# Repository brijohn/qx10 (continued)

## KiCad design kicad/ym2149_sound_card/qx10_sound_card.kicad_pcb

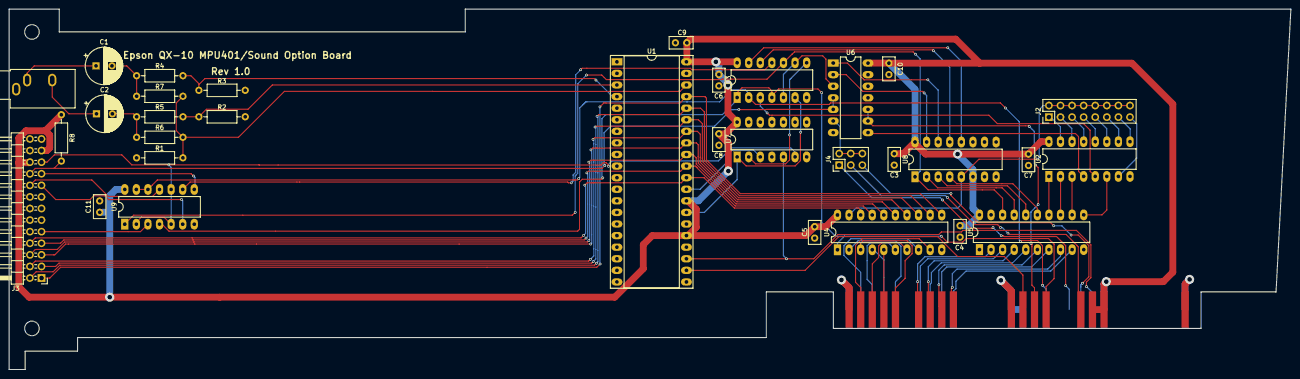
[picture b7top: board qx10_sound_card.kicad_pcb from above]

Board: 2 copper layers, 281.0 x 79.0 mm, 33 parts (0 on the bottom side), 76 nets.

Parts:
C1, C2: 470uF; CP_Radial_D8.0mm_P3.50mm
C3, C4, C5, C6, C7, C8, C9, C10, C11: .1uF; C_Disc_D5.0mm_W2.5mm_P2.50mm
CN1: Edge Connector; BUS_QX10
J1: Speakers; Jack_3.5mm_CUI_SJ1-3533NG_Horizontal
J2: Base Address; PinHeader_2x08_P2.54mm_Vertical
J3: MPU401; PinHeader_2x13_P2.54mm_Horizontal
J4: INT Select; PinHeader_2x03_P2.54mm_Vertical
R1, R2, R3: 3K; R_Axial_DIN0207_L6.3mm_D2.5mm_P10.16mm_Horizontal
R4, R5: 1K; R_Axial_DIN0207_L6.3mm_D2.5mm_P10.16mm_Horizontal
R6, R7: 1K6; R_Axial_DIN0207_L6.3mm_D2.5mm_P10.16mm_Horizontal
R8: 1k; R_Axial_DIN0207_L6.3mm_D2.5mm_P10.16mm_Horizontal
U1: YM2149; DIP-40_W15.24mm_Socket_LongPads
U2, U8: 74LS138; DIP-16_W7.62mm_LongPads
U3, U9: 74LS08; DIP-14_W7.62mm_LongPads
U4: 74LS245; DIP-20_W7.62mm_LongPads
U5: 74LS541; DIP-20_W7.62mm_LongPads
U6: 74LS00; DIP-14_W7.62mm_LongPads
U7: 74LS86; DIP-14_W7.62mm_LongPads

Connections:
+5V: C3.1, C4.1, C5.1, C6.1, C7.1, C8.1, C9.1, C10.1, C11.1, CN1.43, CN1.45, CN1.46, J3.22, J3.23, R8.1, U1.25, U1.28, U1.40, U2.16, U3.14, U4.20, U5.20, U6.14, U7.14, U8.6, U8.16, U9.14
/A0: U3.10, U5.18, U8.1, U9.1
/A1: U5.17, U8.2
/A2: U5.16, U8.3
/A3: U5.15, U8.4
/A4: U2.1, U5.14
/A5: U2.2, U5.13
/A6: U2.3, U5.12
/A7: U2.6, U5.11
/ADR0: CN1.13, U5.2
/ADR1: CN1.14, U5.3
/ADR2: CN1.15, U5.4
/ADR3: CN1.16, U5.5
/ADR4: CN1.17, U5.6
/ADR5: CN1.18, U5.7
/ADR6: CN1.19, U5.8
/ADR7: CN1.20, U5.9
/BC1: U1.29, U7.3
/BDIR: U1.27, U3.6, U7.1
/CHANA: R2.1, R5.2, U1.3
/CHANB: R3.1, R4.2, U1.4
/CHANC: R1.1, R6.2, R7.2, U1.38
/CLK: CN1.31, U1.22
/D0: J3.1, U1.37, U4.11
/D1: J3.2, U1.36, U4.12
/D2: J3.3, U1.35, U4.13
/D3: J3.4, U1.34, U4.14
/D4: J3.5, U1.33, U4.15
/D5: J3.6, U1.32, U4.16
/D6: J3.7, U1.31, U4.17
/D7: J3.8, U1.30, U4.18
/DTB0: CN1.3, U4.9
/DTB1: CN1.4, U4.8
/DTB2: CN1.5, U4.7
/DTB3: CN1.6, U4.6
/DTB4: CN1.7, U4.5
/DTB5: CN1.8, U4.4
/DTB6: CN1.9, U4.3
/DTB7: CN1.10, U4.2
/INTH1: CN1.40, J4.1
/INTH2: CN1.41, J4.3
/INTL: CN1.42, J4.5
/~BSAK: CN1.33, U6.9, U6.10
/~CS: J2.2, J2.4, J2.6, J2.8, J2.10, J2.12, J2.14, J2.16, U4.19, U8.5
/~IRD: CN1.35, U3.1, U3.4, U4.1, U9.4
/~IRQ: J3.20, R8.2, U6.4, U6.5
/~IWR: CN1.36, U3.2, U9.12, U9.13
/~MPU401: U3.11, U9.9
/~RESET: CN1.44, U1.23, U7.5
/~RSET: J3.21, U7.6, U9.2, U9.5, U9.10
/~WR: J3.18, U9.11
GND: C3.2, C4.2, C5.2, C6.2, C7.2, C8.2, C9.2, C10.2, C11.2, CN1.1, CN1.2, CN1.29, CN1.30, CN1.32, CN1.59, CN1.60, J1.S, J3.10, J3.11, J3.24, J3.25, R1.2, R2.2, R3.2, U1.1, U1.24, U1.26, U2.8, U3.7, U4.10, U5.1, U5.10, U5.19, U6.7, U6.12, U6.13, U7.4, U7.7, U7.9, U7.10, U7.12, U7.13, U8.8, U9.7
unnamed: C1.1, J1.T
unnamed: C1.2, R4.1, R7.1
unnamed: C2.1, J1.R
unnamed: C2.2, R5.1, R6.1
unnamed: J2.1, U2.15
unnamed: J2.3, U2.14
unnamed: J2.5, U2.13
unnamed: J2.7, U2.12
unnamed: J2.9, U2.11
unnamed: J2.11, U2.10
unnamed: J2.13, U2.9
unnamed: J2.15, U2.7
unnamed: J3.9, U9.3
unnamed: J3.17, U9.6
unnamed: J3.19, U9.8
unnamed: J4.2, J4.4, J4.6, U6.6
unnamed: U2.4, U6.8
unnamed: U2.5, U3.3
unnamed: U3.5, U3.9, U6.3
unnamed: U3.8, U7.2
unnamed: U3.12, U8.13
unnamed: U3.13, U8.12
unnamed: U6.1, U8.14
unnamed: U6.2, U8.15

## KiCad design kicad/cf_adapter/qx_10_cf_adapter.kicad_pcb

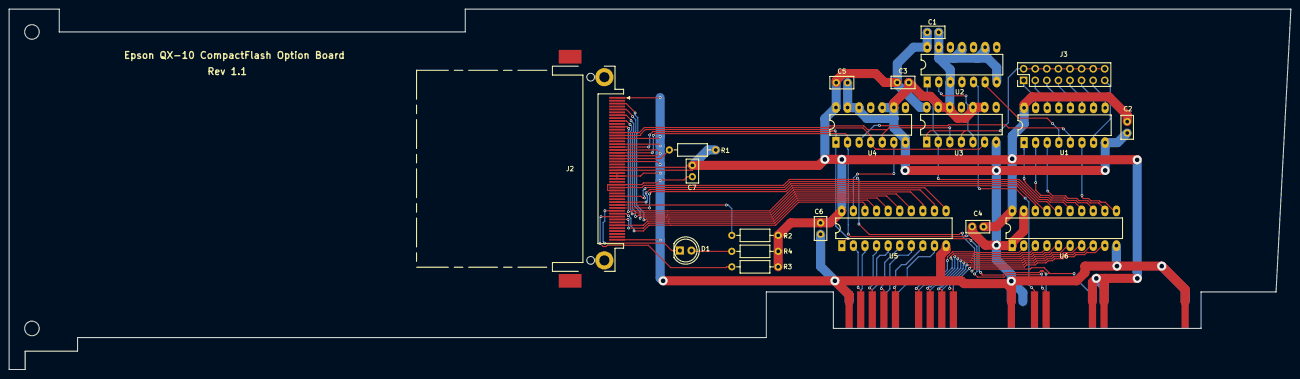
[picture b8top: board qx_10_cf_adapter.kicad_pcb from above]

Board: 2 copper layers, 281.0 x 79.0 mm, 21 parts (0 on the bottom side), 58 nets.

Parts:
C1, C2, C3, C4, C5, C6, C7: .1uf; C_Disc_D5.0mm_W2.5mm_P2.50mm
D1: LED; LED_D5.0mm
J1: Edge Connector; BUS_QX10
J2: CF Connector; CF-Card_3M_N7E50-7516PK-20-WF
J3: Address Jumper; PinHeader_2x08_P2.54mm_Vertical
R1, R2, R3, R4: 1k; R_Axial_DIN0207_L6.3mm_D2.5mm_P10.16mm_Horizontal
U1: 74LS138; DIP-16_W7.62mm_LongPads
U2: 74LS04; DIP-14_W7.62mm_LongPads
U3: 74LS32; DIP-14_W7.62mm_LongPads
U4: 74LS08; DIP-14_W7.62mm_LongPads
U5: 74LS245; DIP-20_W7.62mm_LongPads
U6: 74LS541; DIP-20_W7.62mm_LongPads

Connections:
+5V: C1.1, C2.1, C3.1, C4.1, C5.1, C6.1, C7.1, J1.43, J1.45, J1.46, J2.13, J2.38, R1.1, R2.1, R3.1, R4.1, U1.16, U2.14, U3.14, U4.14, U5.20, U6.20
/A0: J2.20, U6.18
/A1: J2.19, U6.17
/A2: J2.18, U6.16
/A3: U2.1, U3.2, U6.15
/A4: U1.1, U6.14
/A5: U1.2, U6.13
/A6: U1.3, U6.12
/A7: U1.6, U6.11
/ADR0: J1.13, U6.2
/ADR1: J1.14, U6.3
/ADR2: J1.15, U6.4
/ADR3: J1.16, U6.5
/ADR4: J1.17, U6.6
/ADR5: J1.18, U6.7
/ADR6: J1.19, U6.8
/ADR7: J1.20, U6.9
/D0: J2.21, U5.18
/D1: J2.22, U5.17
/D2: J2.23, U5.16
/D3: J2.2, U5.15
/D4: J2.3, U5.14
/D5: J2.4, U5.13
/D6: J2.5, U5.12
/D7: J2.6, U5.11
/DTB0: J1.3, U5.2
/DTB1: J1.4, U5.3
/DTB2: J1.5, U5.4
/DTB3: J1.6, U5.5
/DTB4: J1.7, U5.6
/DTB5: J1.8, U5.7
/DTB6: J1.9, U5.8
/DTB7: J1.10, U5.9
/~BSAK: J1.33, U2.5
/~CS0: J2.7, U3.3, U4.5
/~CS1: J2.32, U3.6, U4.4
/~IRD: J1.35, J2.34, U4.1, U5.1
/~IWR: J1.36, J2.35, U4.2
/~OCS0: J3.2, J3.4, J3.6, J3.8, J3.10, J3.12, J3.14, J3.16, U3.1, U3.4
/~RSET: J1.44, J2.41
GND: C1.2, C2.2, C3.2, C4.2, C5.2, C6.2, C7.2, J1.1, J1.2, J1.29, J1.30, J1.32, J1.59, J1.60, J2.1, J2.8, J2.9, J2.10, J2.11, J2.12, J2.14, J2.15, J2.16, J2.17, J2.39, J2.50, U1.8, U2.3, U2.7, U2.9, U2.11, U2.13, U3.7, U3.9, U3.10, U3.12, U3.13, U4.7, U4.9, U4.10, U4.12, U4.13, U5.10, U6.1, U6.10, U6.19
unnamed: D1.1, J2.45
unnamed: D1.2, R4.2
unnamed: J2.36, R1.2
unnamed: J2.44, R2.2
unnamed: J2.46, R3.2
unnamed: J3.1, U1.15
unnamed: J3.3, U1.14
unnamed: J3.5, U1.13
unnamed: J3.7, U1.12
unnamed: J3.9, U1.11
unnamed: J3.11, U1.10
unnamed: J3.13, U1.9
unnamed: J3.15, U1.7
unnamed: U1.4, U2.6
unnamed: U1.5, U4.3
unnamed: U2.2, U3.5
unnamed: U4.6, U5.19

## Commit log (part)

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2019-11-14 bios: add disassembly of qx-10 bios.sys (2.20)
2021-01-21 Added table listing of the IO ports on the QX-10
2021-01-21 bios: Fix comment in bios.asm
2021-01-21 bios: Update symbol table
2021-07-12 Add gitattributes file
2021-07-12 bios: Add nec765 param table comments and symbol
2021-07-12 docs: add pdf documentation/datasheets
2021-07-12 schematics: Add Q10MF multifont option card schematic
2022-01-10 bios: Comment memory block copy routine
2022-01-10 bios: Minor update to symbols.lst
2022-01-10 bios: Comment assembly for jump/call code in another bank
2022-03-29 docs: Add QX-10/16 technical manuals
2022-03-29 cpm: add mpu401 test program
2022-03-29 cpm: Add compact flash utilities
2022-03-29 msdos: Add driver for cfide adapter and cfformat module
2022-04-01 diskimages: add msdos and cpm disk images
2022-04-01 kicad: Add ym2149 sound card
2022-04-01 kicad: Add kicad design files for compact flash adapter
2022-04-12 kicad: Add template for creating option cards
2022-04-12 Add .gitignore
2022-04-12 bios: Add rough dissassembly for bios2.sys
2022-04-12 kicad: Add clone of comrex cr1510 adapter card
2022-05-18 kicad: Initial schematic for the Titan QX-PC expansion card
2022-05-24 kicad: Add Titan QXPC Memory board schematics
2022-05-29 kicad: Initial board layout for titan memory board
2022-06-22 kicad: Add some notes to titan qxpc schematic
2022-07-09 kicad: Add a few more notes to titan qxpc schematic
2022-07-09 kicad: Create clone version of titan qxpc using SRAM
2022-10-13 kicad: Route QXPC Clone PCB and update BOM
2022-10-22 diskimages: Add titan qx-pc diskimage
2022-10-22 firmware: Add firmware files for Titan QX-PC Clone
2022-11-29 kicad: Add QX10 1MB memory expansion card
2023-08-29 cpm: Update compact flash utilities to support LBA addressing
2023-08-31 bios: Update to use LBA addressing for CF card
    Add patches and makefile to allow easy rebuilding of cpm2.sys
2023-08-31 diskimages: Add disk image compiled to use LBA for CF card access
2023-09-04 bios: Update CP/M and utils to use 8 MB partitions
2023-09-04 diskimages: Update LBA disk image (increase partitions to 8MB)
2023-09-05 cpm: Add tune.asm for playing PT3, PT2, and MYM files
2023-09-06 diskimages: cleanup cp/m disk images
2023-09-06 cpm: Fix cfformat when compiled with CHS flag
2023-09-06 kicad: update PLCC socket part numbers for memory expansion board
2023-09-12 cpm: add cqgtest.z80 to test memory expansion board
2023-09-15 diskimages: Add cqgtest.com to CP/M diskimages
2024-02-19 bios: Add CompactFlash LBA patches to bios version 2.27 * This version supports the QX-16
2024-02-19 diskimages: Add disk image for CPM 2.27 (QX-10/16)
2024-02-19 docs: Add CR-103 Modem documenation
2024-07-19 kicad: Schematic and firmware for a keyboard adapter.
2025-08-18 kicad: Add modern multifont clone and firmware.
2025-08-18 kicad: Update parts list for multifont card
2026-02-01 cpm: Added modified QX-16 IPL 3.0A source that allows booting from CompactFlash
2026-02-01 diskimages: Update QX-16 CP/M diskimage to support booting from CompactFlash
2026-02-01 bios: add hdpart.com patches to fix hdbooting from CF
2026-02-01 bios: update 2.27 patches to fix cf boot hang
2026-02-01 diskimages: Update qx16lba disk image current cpm2.sys and utilities
2026-02-01 cpm: Update cfformat utility for bios 2.27
2026-02-01 bios: Add disassembly for version B2.27 resident bios
2026-02-01 cpm: Add cmosload, cmosdump, and loadrom utilities
2026-02-01 diskimages: Remove obsolete disk images from repo
2026-02-20 cpm: Added IPL006CF source containing modifications to alllow a QX-10 to boot from CF
2026-02-22 kicad: Update titan clone to kicad 9 and add BOM CSV
2026-02-24 build: Added internal build tools
2026-02-24 bios: Update Makefiles to use zmac for assembly
2026-02-24 cpm: Update CP/M apps to use zmac for assembly
2026-02-24 cpm: Add Makefile for IPL/LDR code
2026-02-24 build: Add toplevel Makefile
2026-02-24 cpm: Add speech program
2026-02-25 bios: Patch hdpart.com to always display full UI on a QX10
2026-03-01 bios: Fix bug in hdpart cmos code
2026-03-02 bios: patch qxdisk.com and qxpc.com to support compact flash
2026-03-02 diskimages: update cpm disk images
    * Add qx10lba.imd (uses ports 0x8x instead of 0xDx)
    * Update qx16lba.imd with updated software
2026-03-02 bios: Forgot to include virgin copies of qxdisk.com/qxpc.com
